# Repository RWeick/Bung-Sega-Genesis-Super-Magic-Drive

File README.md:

# Bung-Sega-Genesis-Super-Magic-Drive
The bioses and Kicad files for the Bung Super Magic Drive for the Sega Genesis

PCB Thicknesses are documented in the Kicad files.

The motherboard contains two modifications from the original: a bodged resistor pack now has its own footprint and there is a solder jumper to switch between original 16M RAM mode and 32M RAM mode. The 32M RAM mode was a modification that would be done when you sent your system back to Bung for the upgrade. Unfortunately it appears that the upgrade also required the CPLD to be upgraded as well, and a modified CPLD has not yet surfaced to be studied. The upgrade solder jumper and 32M RAM board are therefore provided for a future point where the CPLD is found, studied, and reverse engineered. You may use a 32M RAM card with this system, but it will only register 16M of RAM.

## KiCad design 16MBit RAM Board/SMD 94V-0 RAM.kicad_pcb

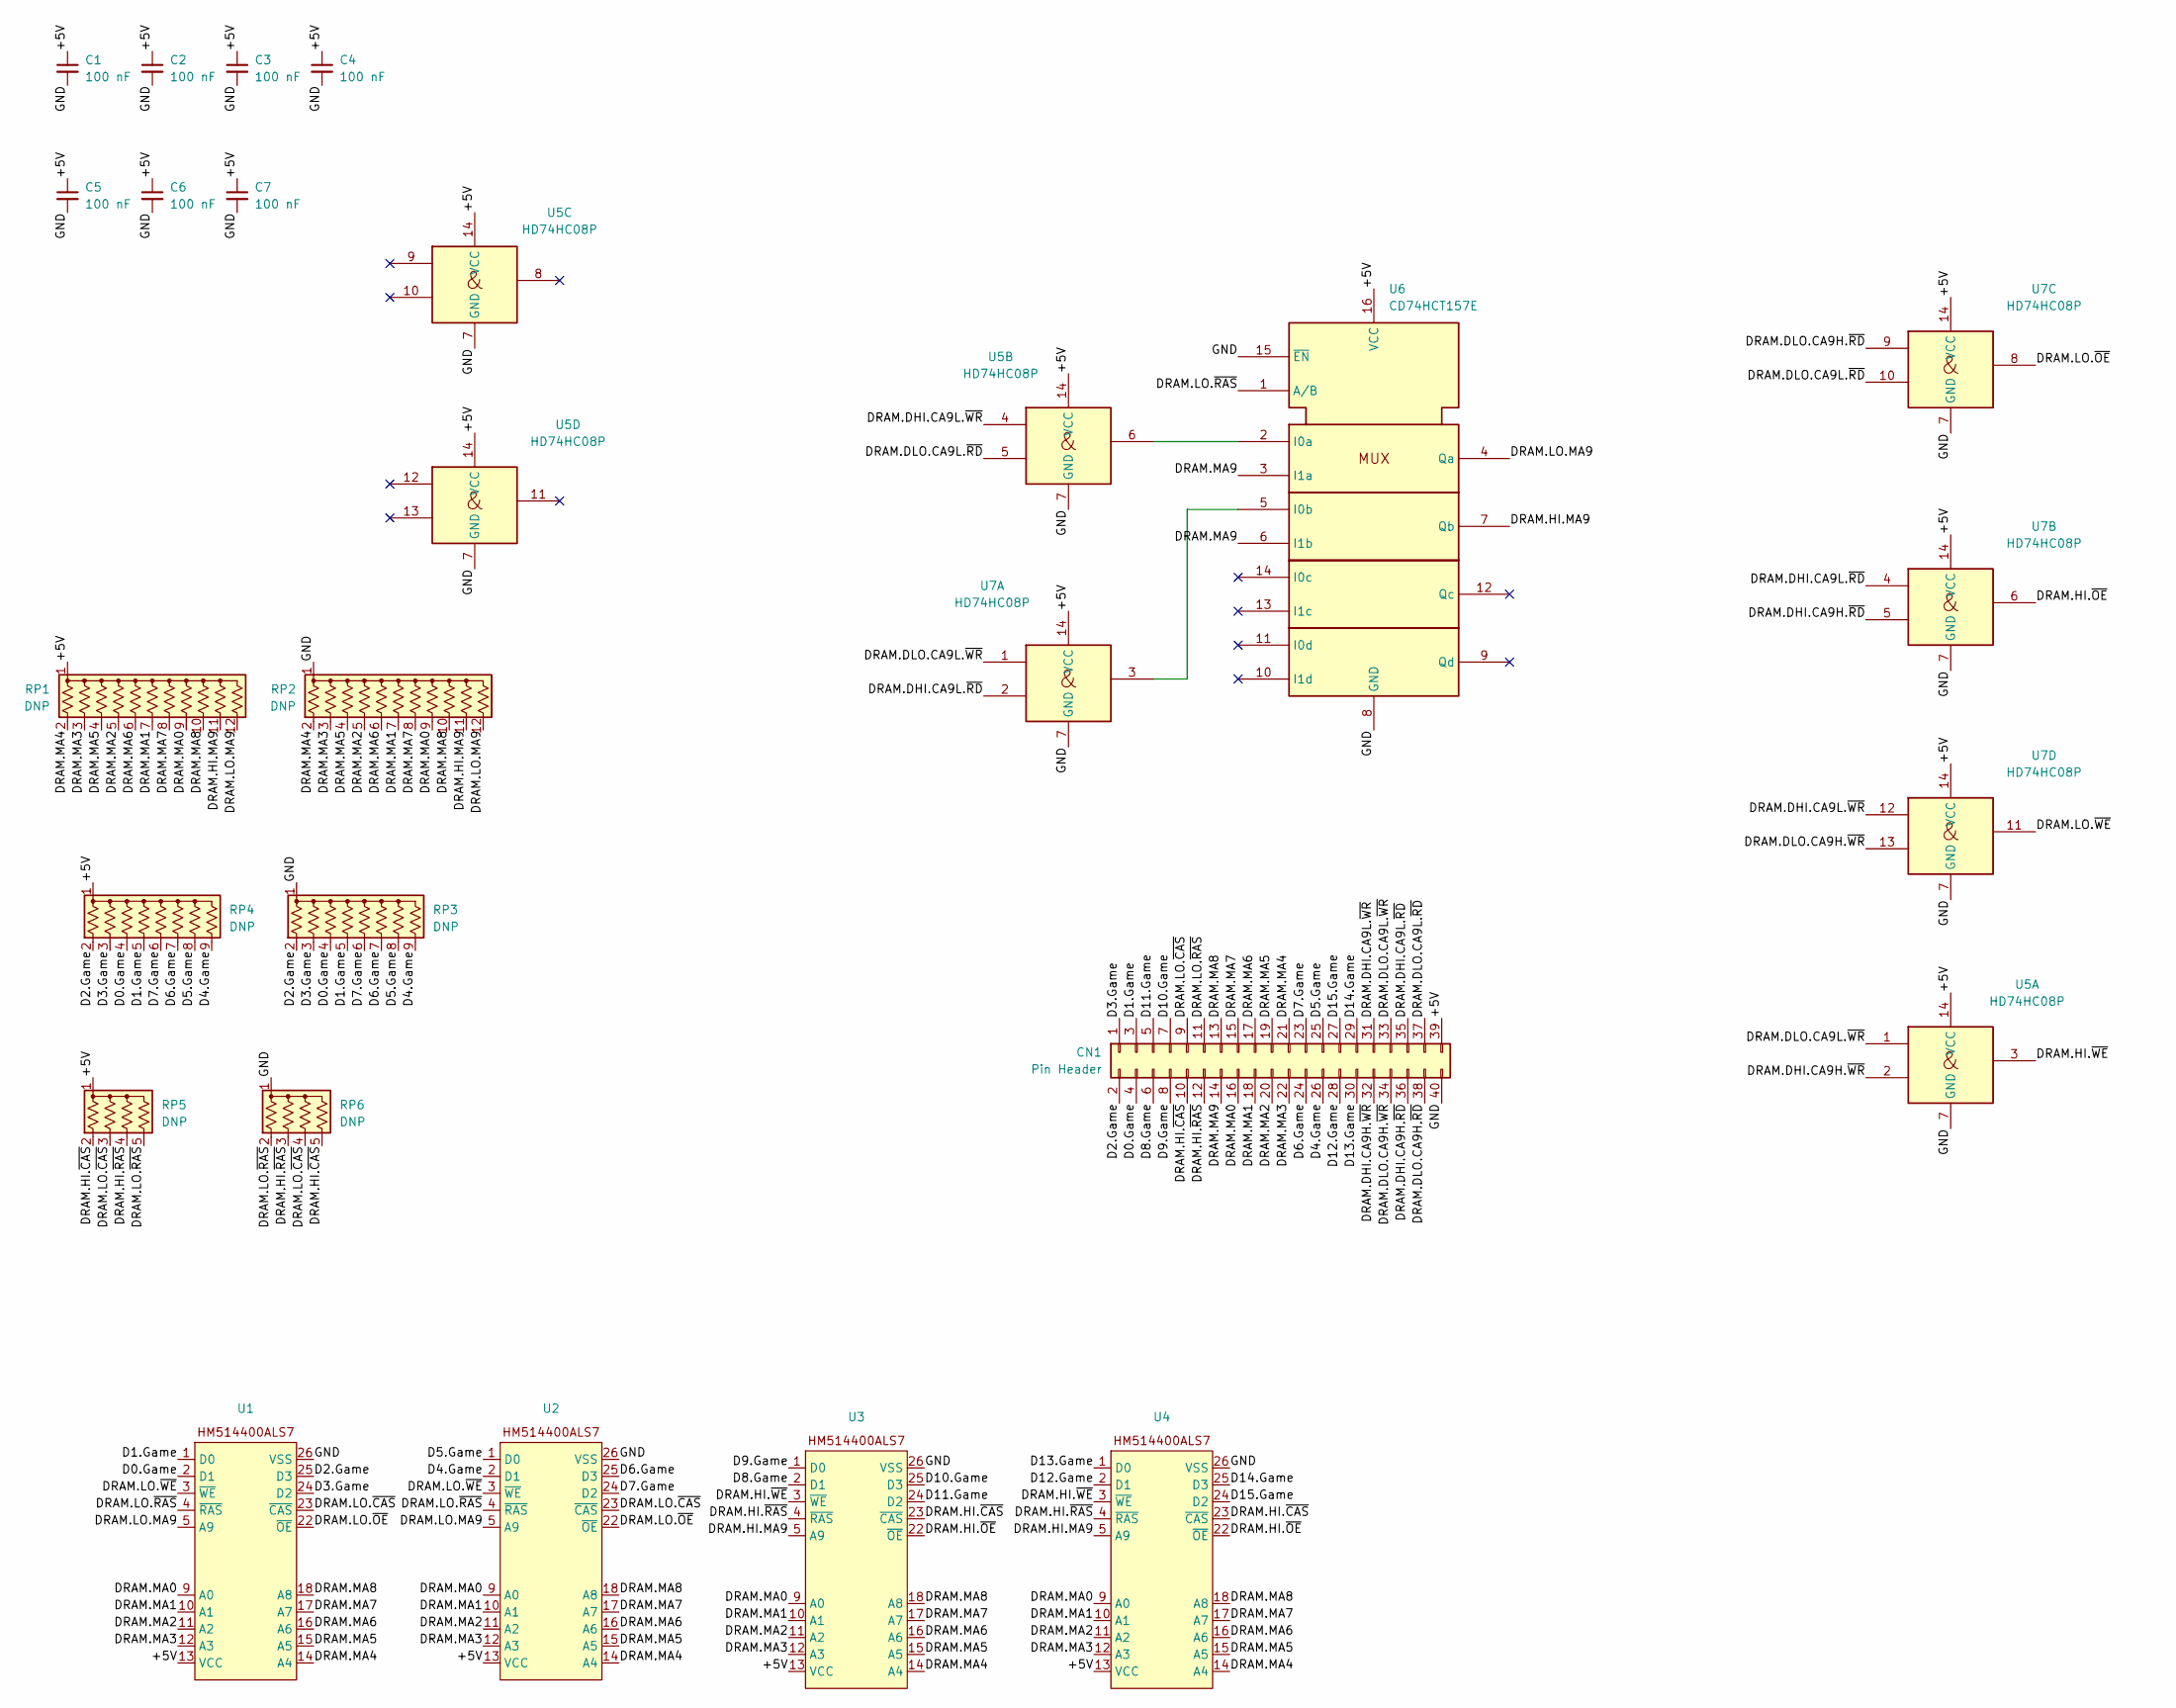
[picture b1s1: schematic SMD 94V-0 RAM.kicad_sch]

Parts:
C1, C2, C3, C4, C5, C6, C7: 100 nF
CN1: Pin Header
RP1, RP2: DNP; R_Array_SIP12
RP3, RP4: DNP; R_Array_SIP9
RP5, RP6: DNP; R_Array_SIP5
U1, U2, U3, U4: (no value)
U5, U7: HD74HC08P
U6: CD74HCT157E

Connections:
/+5V: C1.1, C2.1, C3.1, C4.1, C5.1, C6.1, C7.1, CN1.39, RP1.1 (common), RP4.1 (common), RP5.1 (common), U1.13 (VCC), U2.13 (VCC), U3.13 (VCC), U4.13 (VCC), U5.14 (VCC), U6.16 (VCC), U7.14 (VCC)
/A0: CN1.16, RP1.9 (R8), RP2.9 (R8), U1.9 (A0), U2.9 (A0), U3.9 (A0), U4.9 (A0)
/A1: CN1.18, RP1.7 (R6), RP2.7 (R6), U1.10 (A1), U2.10 (A1), U3.10 (A1), U4.10 (A1)
/A2: CN1.20, RP1.5 (R4), RP2.5 (R4), U1.11 (A2), U2.11 (A2), U3.11 (A2), U4.11 (A2)
/A3: CN1.22, RP1.3 (R2), RP2.3 (R2), U1.12 (A3), U2.12 (A3), U3.12 (A3), U4.12 (A3)
/A4: CN1.21, RP1.2 (R1), RP2.2 (R1), U1.14 (A4), U2.14 (A4), U3.14 (A4), U4.14 (A4)
/A5: CN1.19, RP1.4 (R3), RP2.4 (R3), U1.15 (A5), U2.15 (A5), U3.15 (A5), U4.15 (A5)
/A6: CN1.17, RP1.6 (R5), RP2.6 (R5), U1.16 (A6), U2.16 (A6), U3.16 (A6), U4.16 (A6)
/A7: CN1.15, RP1.8 (R7), RP2.8 (R7), U1.17 (A7), U2.17 (A7), U3.17 (A7), U4.17 (A7)
/A8: CN1.13, RP1.10 (R9), RP2.10 (R9), U1.18 (A8), U2.18 (A8), U3.18 (A8), U4.18 (A8)
/A9: CN1.14, U6.3 (I1a), U6.6 (I1b)
/GND: C1.2, C2.2, C3.2, C4.2, C5.2, C6.2, C7.2, CN1.40, RP2.1 (common), RP3.1 (common), RP6.1 (common), U1.26 (VSS), U2.26 (VSS), U3.26 (VSS), U4.26 (VSS), U5.7 (GND), U6.8 (GND), U6.15 (~EN), U7.7 (GND)
/RAM1-2.~OE: CN1.38, U7.9
/RAM3-4.~OE: CN1.36, U7.5
/RAM.Bank.1.~OE: CN1.35, U7.2, U7.4
/RAM.Bank.1.~WE: CN1.34, U7.13
/RAM.Bank.2.~OE: CN1.37, U5.5, U7.10
/RAM.Bank.2.~WE: CN1.32, U5.2
/U1-2.A9.~WE.EN: CN1.31, U5.4, U7.12
/U1-U2.A9: RP1.12 (R11), RP2.12 (R11), U1.5 (A9), U2.5 (A9), U6.4 (Qa)
/U1-U2.~CAS: CN1.9, RP5.3 (R2), RP6.4 (R3), U1.23 (~CAS), U2.23 (~CAS)
/U1-U2.~OE: U1.22 (~OE), U2.22 (~OE), U7.8
/U1-U2.~RAS: CN1.11, RP5.5 (R4), RP6.2 (R1), U1.4 (~RAS), U2.4 (~RAS), U6.1 (A/B)
/U1-U2.~WE: U1.3 (~WE), U2.3 (~WE), U7.11
/U1.D0: CN1.3, RP3.5 (R4), RP4.5 (R4), U1.1 (D0)
/U1.D1: CN1.4, RP3.4 (R3), RP4.4 (R3), U1.2 (D1)
/U1.D2: CN1.1, RP3.3 (R2), RP4.3 (R2), U1.24 (D2)
/U1.D3: CN1.2, RP3.2 (R1), RP4.2 (R1), U1.25 (D3)
/U2.D0: CN1.25, RP3.8 (R7), RP4.8 (R7), U2.1 (D0)
/U2.D1: CN1.26, RP3.9 (R8), RP4.9 (R8), U2.2 (D1)
/U2.D2: CN1.23, RP3.6 (R5), RP4.6 (R5), U2.24 (D2)
/U2.D3: CN1.24, RP3.7 (R6), RP4.7 (R6), U2.25 (D3)
/U3-4.A9.~WE.EN: CN1.33, U5.1, U7.1
/U3-U4.A9: RP1.11 (R10), RP2.11 (R10), U3.5 (A9), U4.5 (A9), U6.7 (Qb)
/U3-U4.~CAS: CN1.10, RP5.2 (R1), RP6.5 (R4), U3.23 (~CAS), U4.23 (~CAS)
/U3-U4.~OE: U3.22 (~OE), U4.22 (~OE), U7.6
/U3-U4.~RAS: CN1.12, RP5.4 (R3), RP6.3 (R2), U3.4 (~RAS), U4.4 (~RAS)
/U3-U4.~WE: U3.3 (~WE), U4.3 (~WE), U5.3
/U3.D0: CN1.8, U3.1 (D0)
/U3.D1: CN1.6, U3.2 (D1)
/U3.D2: CN1.5, U3.24 (D2)
/U3.D3: CN1.7, U3.25 (D3)
/U4.D0: CN1.30, U4.1 (D0)
/U4.D1: CN1.28, U4.2 (D1)
/U4.D2: CN1.27, U4.24 (D2)
/U4.D3: CN1.29, U4.25 (D3)
unnamed: U5.6, U6.2 (I0a)
unnamed: U6.5 (I0b), U7.3

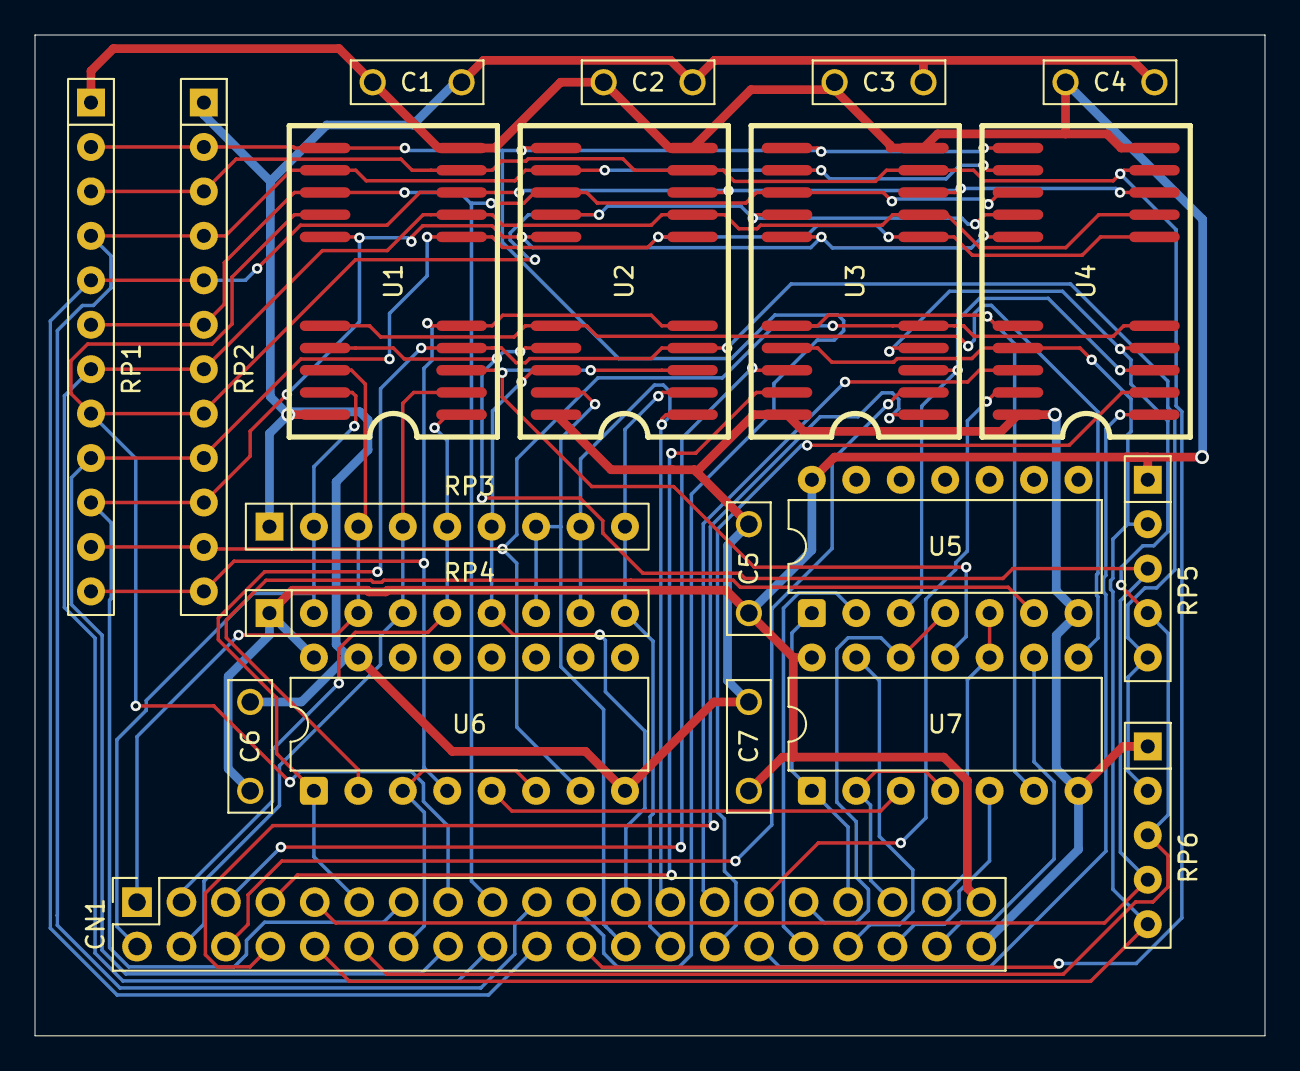
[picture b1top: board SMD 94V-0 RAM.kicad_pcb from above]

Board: 2 copper layers, 70.3 x 57.2 mm, 21 parts (0 on the bottom side), 48 nets.

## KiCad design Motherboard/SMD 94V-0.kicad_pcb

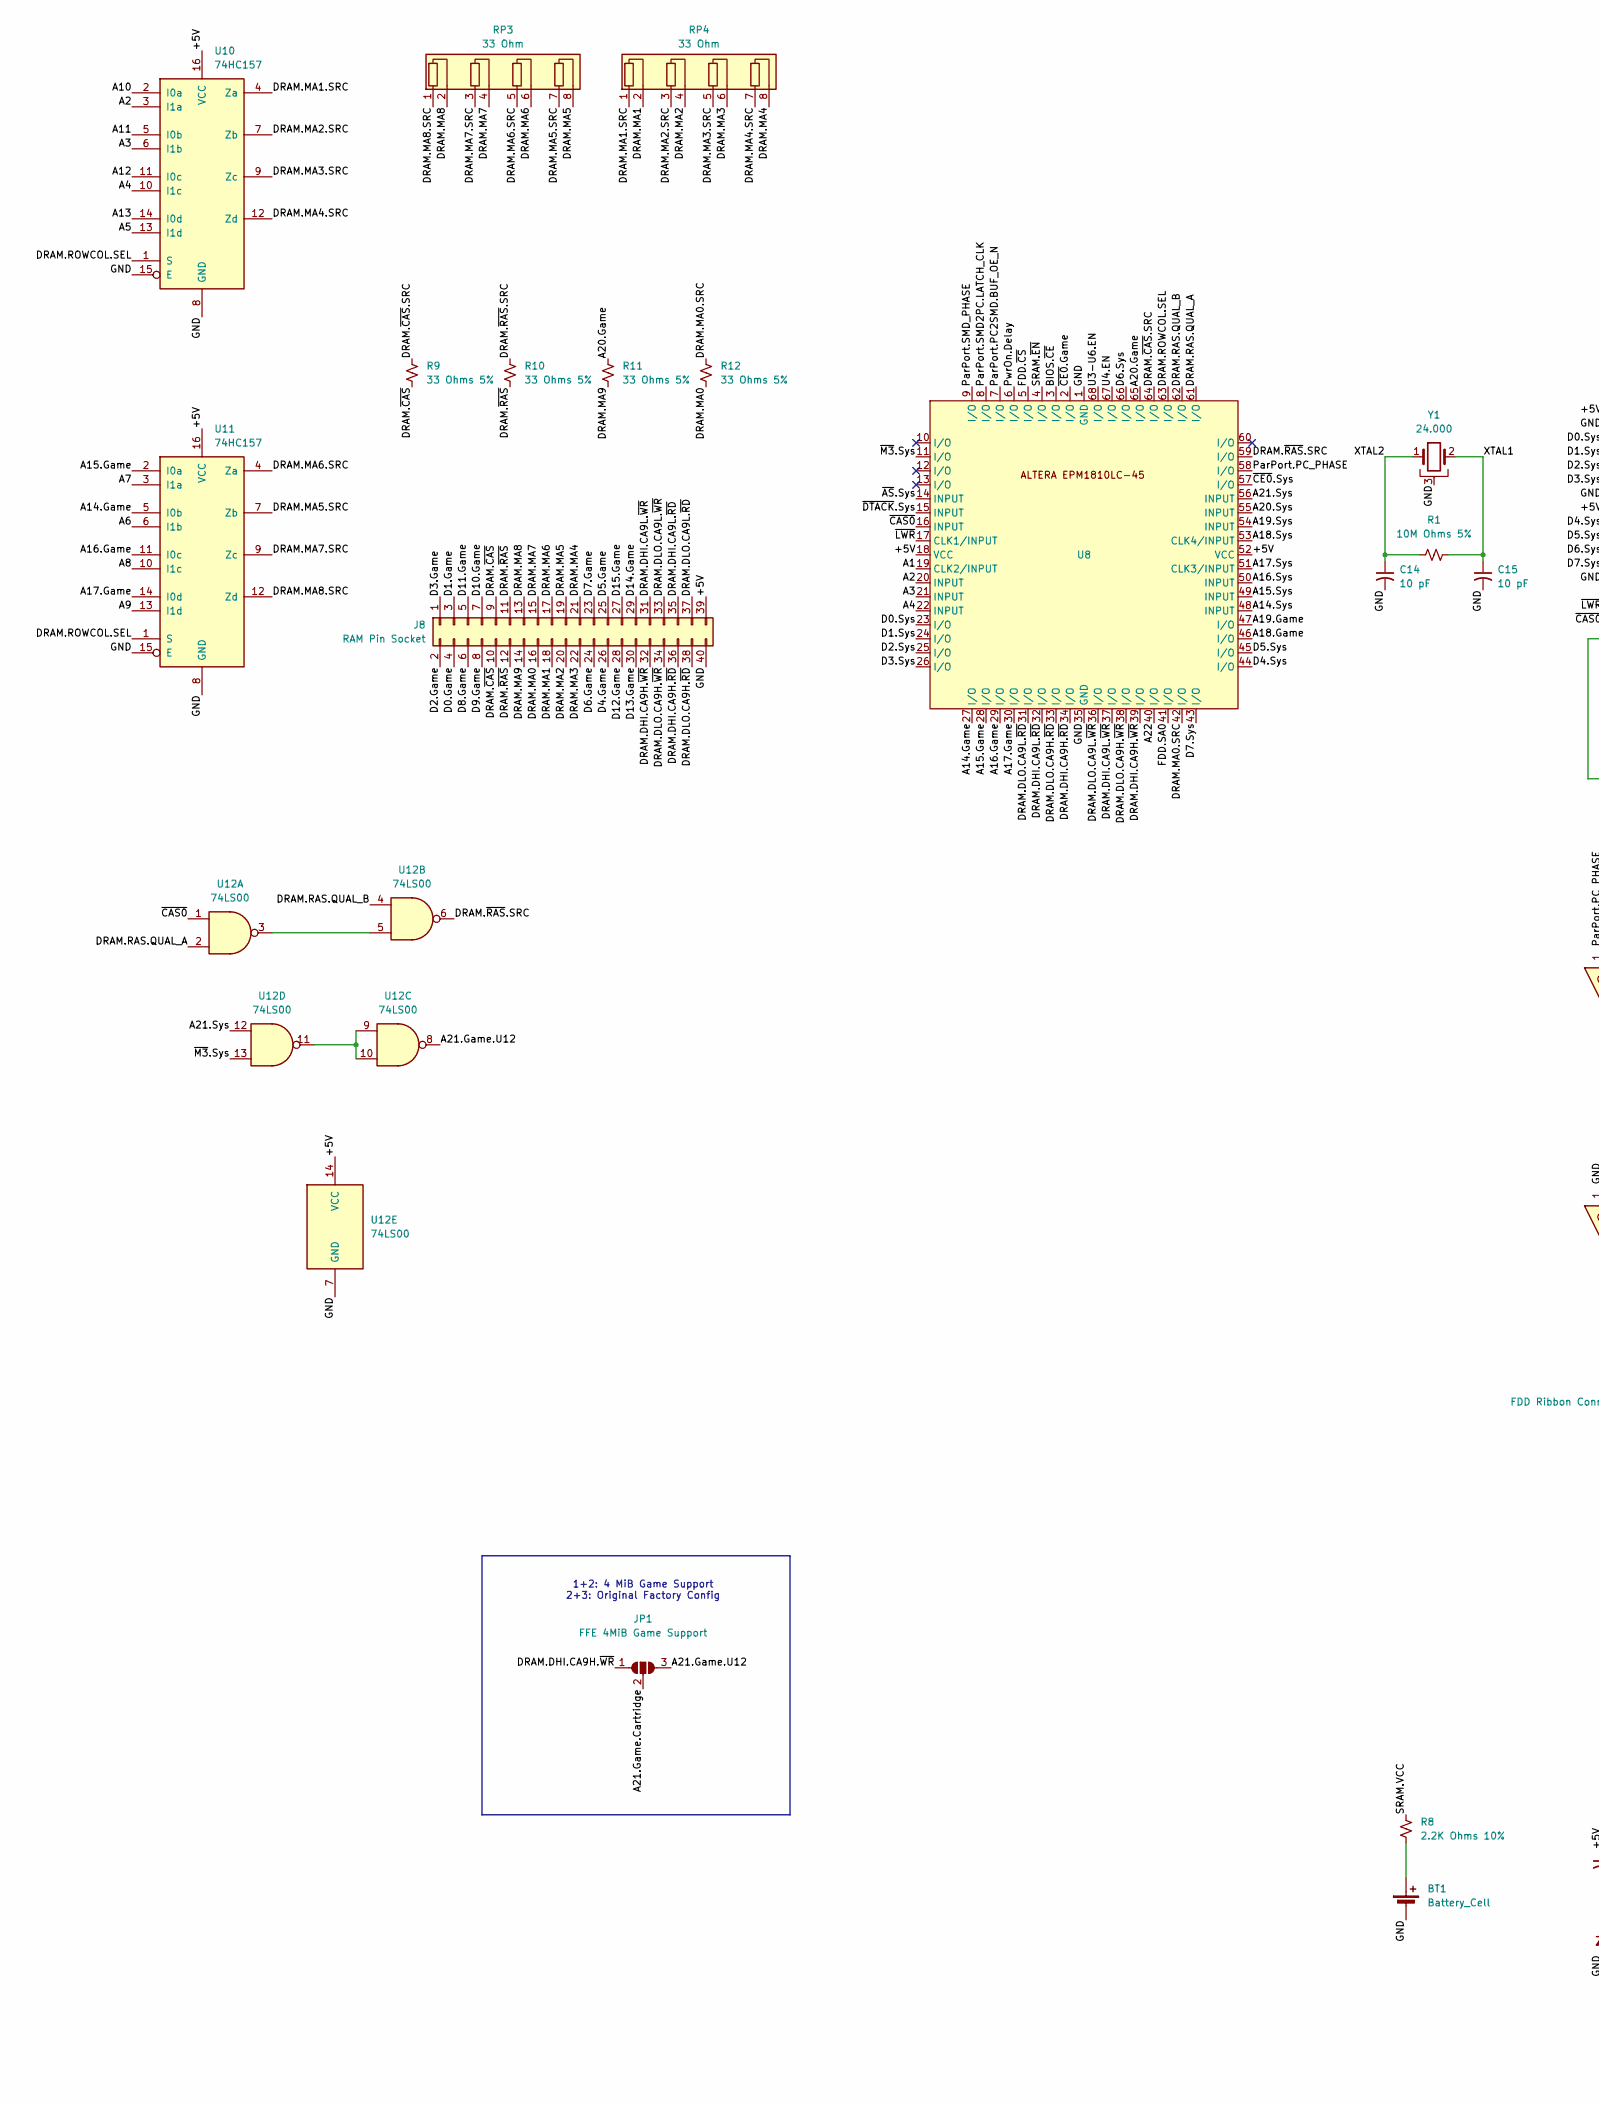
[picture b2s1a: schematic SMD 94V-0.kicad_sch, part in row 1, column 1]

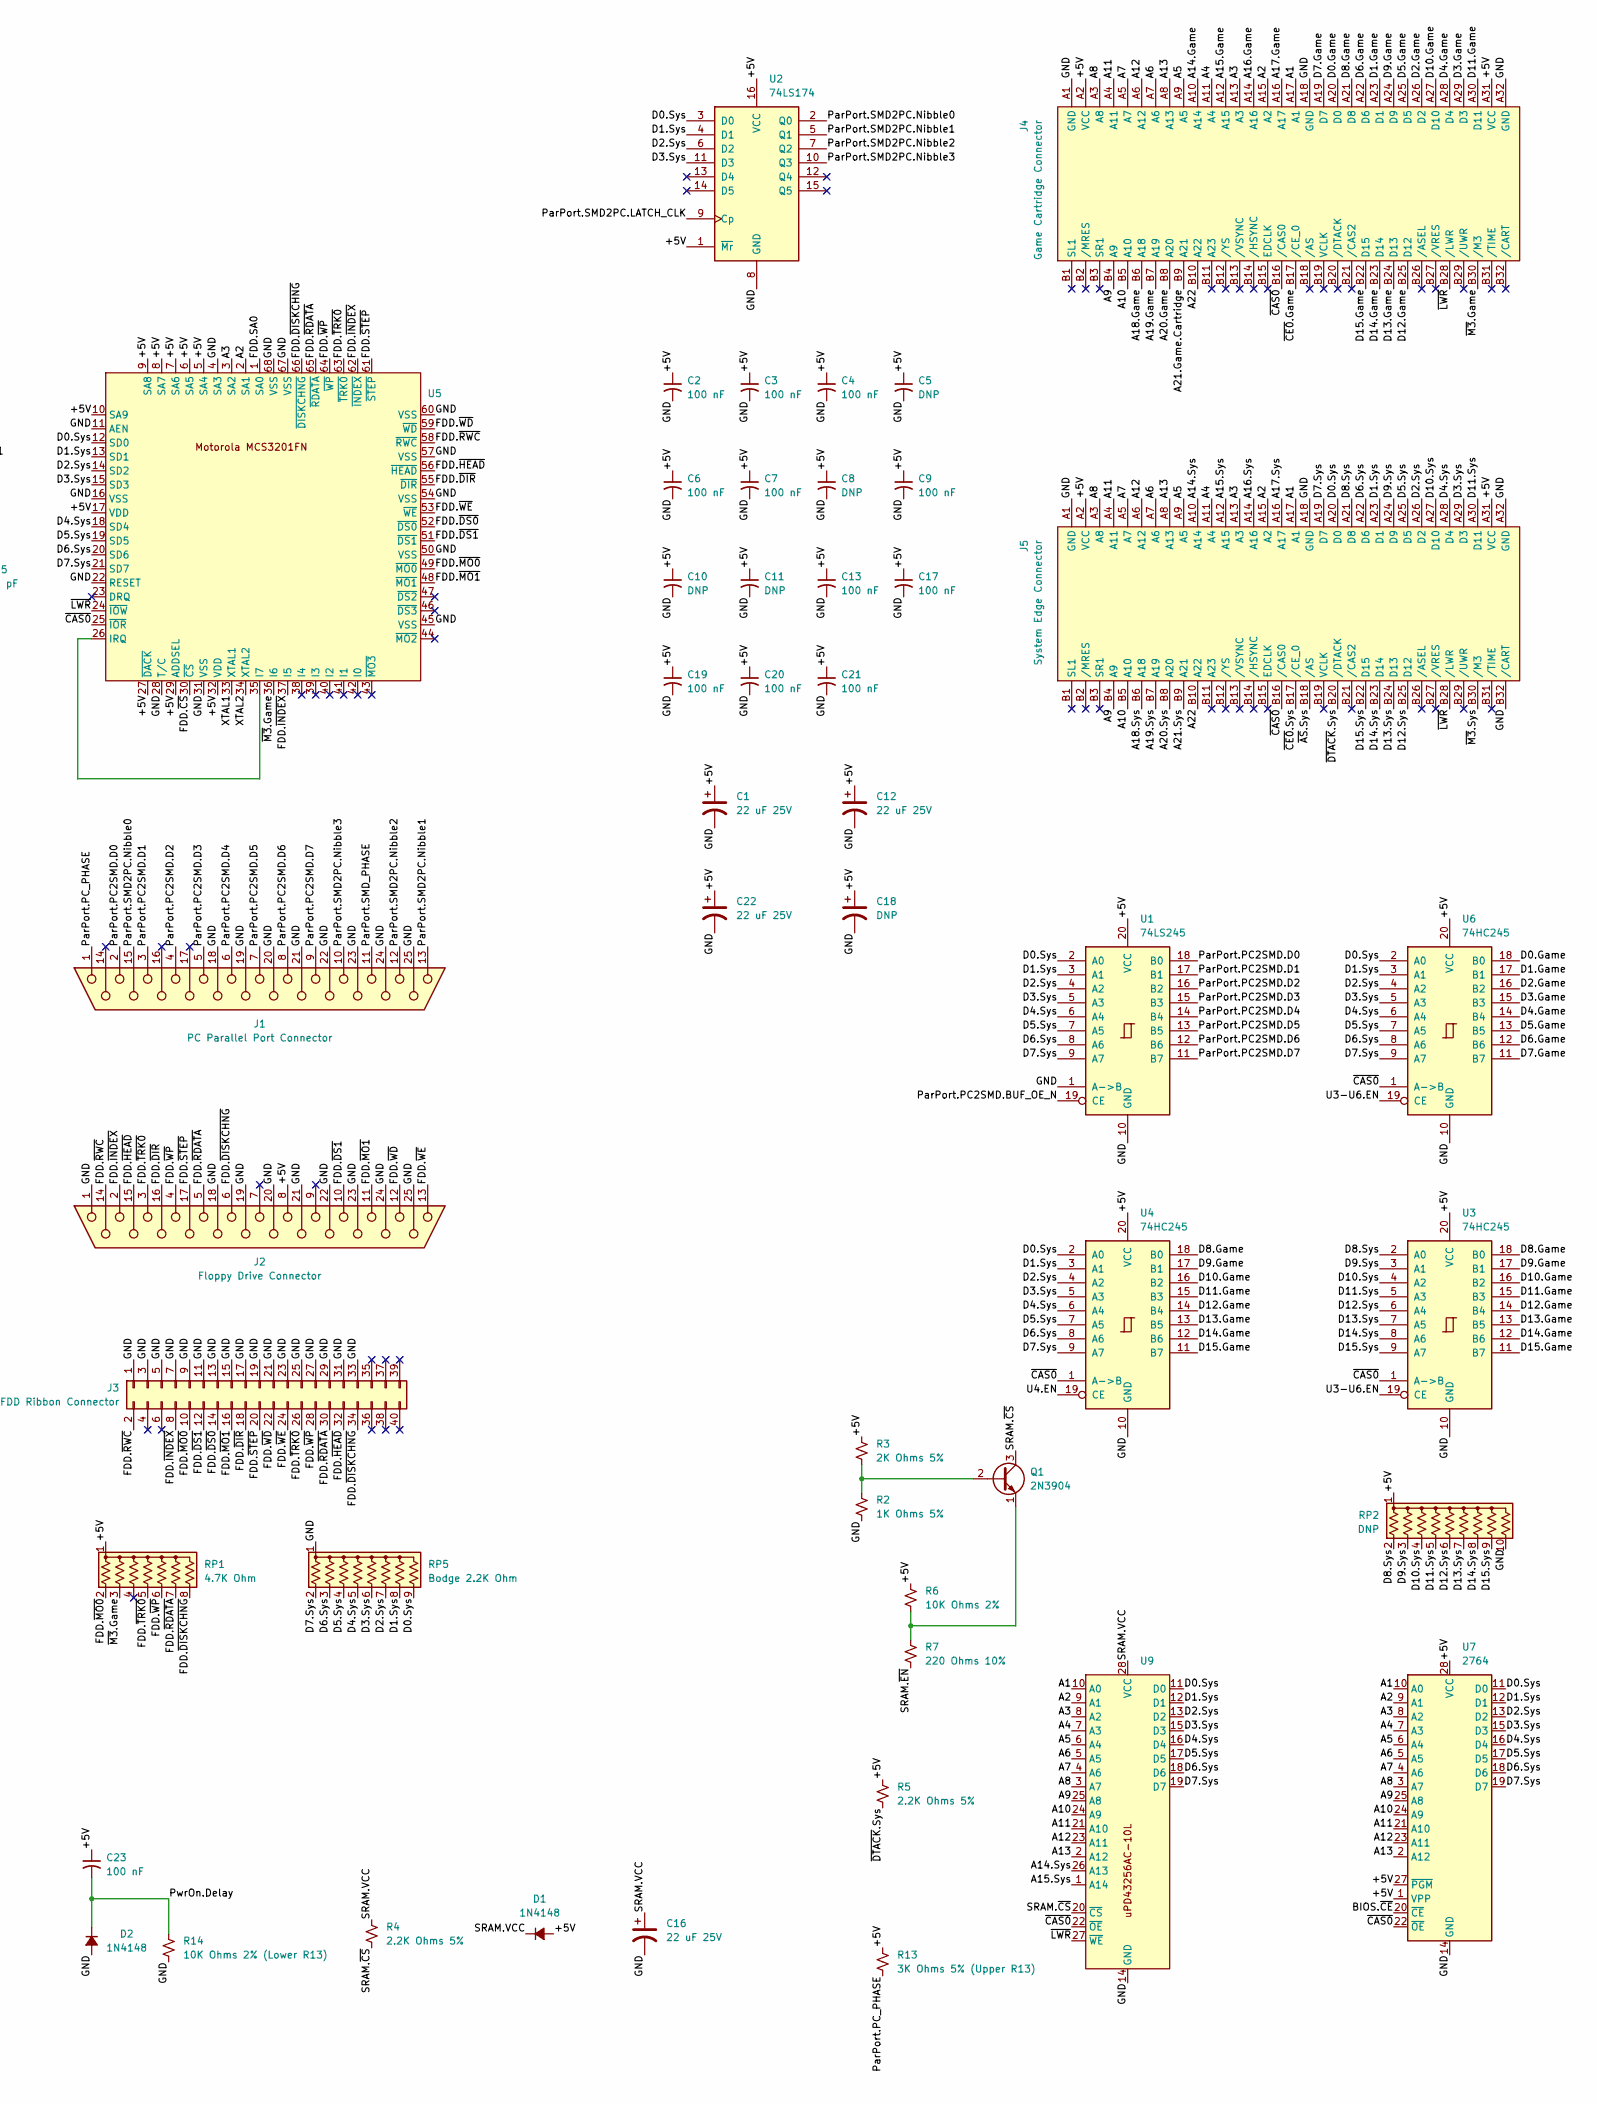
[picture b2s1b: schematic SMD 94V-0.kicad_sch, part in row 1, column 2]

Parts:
BT1: Battery_Cell; Battery
C1, C12, C16, C22: 22 uF 25V; CP_Radial_D5.0mm_P2.50mm
C2, C3, C4, C6, C7, C9, C13, C17, C19, C20, C21, C23: 100 nF; Capacitor
C5, C8, C10, C11: DNP; Capacitor
C14, C15: 10 pF; Capacitor
C18: DNP; CP_Radial_D5.0mm_P2.50mm
D1, D2: 1N4148; Diode
J1: PC Parallel Port Connector; DSUB-25_Socket_Horizontal_P2.77x2.84mm_EdgePinOffset7.70mm_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
J2: Floppy Drive Connector; DSUB-25_Socket_Horizontal_P2.77x2.84mm_EdgePinOffset7.70mm_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
J3: FDD Ribbon Connector; PinHeader_2x20_P2.54mm_Vertical
J4: Game Cartridge Connector; Cartridge Slot
J5: System Edge Connector; PinHeader_2x32_P2.54mm_Vertical
J8: RAM Pin Socket; PinHeader_2x20_P2.54mm_Vertical
JP1: FFE 4MiB Game Support; SolderJumper-3_P1.3mm_Open_RoundedPad1.0x1.5mm_NumberLabels
Q1: 2N3904; Transistor
R1: 10M Ohms 5%; Resistor
R2: 1K Ohms 5%; Resistor
R3: 2K Ohms 5%; Resistor
R4, R5: 2.2K Ohms 5%; Resistor
R6: 10K Ohms 2%; Resistor
R7: 220 Ohms 10%; Resistor
R8: 2.2K Ohms 10%; Resistor
R9, R10, R11, R12: 33 Ohms 5%; Resistor
R13: 3K Ohms 5% (Upper R13); Resistor
R14: 10K Ohms 2% (Lower R13); Resistor
RP1: 4.7K Ohm; R_Array_SIP8
RP2: DNP; R_Array_SIP10
RP3, RP4: 33 Ohm; R_Array_SIP8
RP5: Bodge 2.2K Ohm; R_Array_SIP9
U1: 74LS245; DIP-20_W7.62mm
U2: 74LS174; DIP-16_W7.62mm
U3, U4, U6: 74HC245; DIP-20_W7.62mm
U5, U8: PLCC-68_THT-Socket
U7: 2764; DIP-28_W15.24mm
U9: DIP-28_W15.24mm
U10, U11: 74HC157; DIP-16_W7.62mm
U12: 74LS00; DIP-14_W7.62mm
Y1: 24.000; Crystal_HC18-U_Horizontal_1EP_style2

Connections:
/+5V: C1.1, C2.1, C3.1, C4.1, C5.1, C6.1, C7.1, C8.1, C9.1, C10.1, C11.1, C12.1, C13.1, C17.1, C18.1, C19.1, C20.1, C21.1, C22.1, C23.1, D1.2 (A), J2.8, J4.A2 (VCC), J4.A31 (VCC), J5.A2 (VCC), J5.A31 (VCC), J8.39, R3.1, R5.1, R6.1, R13.1, RP1.1 (common), RP2.1 (common), U1.20 (VCC), U2.1 (~Mr), U2.16 (VCC), U3.20 (VCC), U4.20 (VCC), U5.5 (SA4), U5.6 (SA5), U5.7 (SA6), U5.8 (SA7), U5.9 (SA8), U5.10 (SA9), U5.17 (VDD), U5.27 (~DACK), U5.29 (ADDSEL), U5.32 (VDD), U6.20 (VCC), U7.1 (VPP), U7.27 (~PGM), U7.28 (VCC), U8.18 (VCC), U8.52 (VCC), U10.16 (VCC), U11.16 (VCC), U12.14 (VCC)
/A1: J4.A17 (A1), J5.A17 (A1), U7.10 (A0), U8.19 (CLK2/INPUT), U9.10 (A0)
/A2: J4.A15 (A2), J5.A15 (A2), U5.2 (SA1), U7.9 (A1), U8.20 (INPUT), U9.9 (A1), U10.3 (I1a)
/A3: J4.A13 (A3), J5.A13 (A3), U5.3 (SA2), U7.8 (A2), U8.21 (INPUT), U9.8 (A2), U10.6 (I1b)
/A4: J4.A11 (A4), J5.A11 (A4), U7.7 (A3), U8.22 (INPUT), U9.7 (A3), U10.10 (I1c)
/A5: J4.A9 (A5), J5.A9 (A5), U7.6 (A4), U9.6 (A4), U10.13 (I1d)
/A6: J4.A7 (A6), J5.A7 (A6), U7.5 (A5), U9.5 (A5), U11.6 (I1b)
/A7: J4.A5 (A7), J5.A5 (A7), U7.4 (A6), U9.4 (A6), U11.3 (I1a)
/A8: J4.A3 (A8), J5.A3 (A8), U7.3 (A7), U9.3 (A7), U11.10 (I1c)
/A9: J4.B4 (A9), J5.B4 (A9), U7.25 (A8), U9.25 (A8), U11.13 (I1d)
/A10: J4.B5 (A10), J5.B5 (A10), U7.24 (A9), U9.24 (A9), U10.2 (I0a)
/A11: J4.A4 (A11), J5.A4 (A11), U7.21 (A10), U9.21 (A10), U10.5 (I0b)
/A12: J4.A6 (A12), J5.A6 (A12), U7.23 (A11), U9.23 (A11), U10.11 (I0c)
/A13: J4.A8 (A13), J5.A8 (A13), U7.2 (A12), U9.2 (A12), U10.14 (I0d)
/A14.Game: J4.A10 (A14), U8.27 (I/O), U11.5 (I0b)
/A14.Sys: J5.A10 (A14), U8.48 (INPUT), U9.26 (A13)
/A15.Game: J4.A12 (A15), U8.28 (I/O), U11.2 (I0a)
/A15.Sys: J5.A12 (A15), U8.49 (INPUT), U9.1 (A14)
/A16.Game: J4.A14 (A16), U8.29 (I/O), U11.11 (I0c)
/A16.Sys: J5.A14 (A16), U8.50 (INPUT)
/A17.Game: J4.A16 (A17), U8.30 (I/O), U11.14 (I0d)
/A17.Sys: J5.A16 (A17), U8.51 (CLK3/INPUT)
/A18.Game: J4.B6 (A18), U8.46 (I/O)
/A18.Sys: J5.B6 (A18), U8.53 (CLK4/INPUT)
/A19.Game: J4.B7 (A19), U8.47 (I/O)
/A19.Sys: J5.B7 (A19), U8.54 (INPUT)
/A20.Game: J4.B8 (A20), R11.1, U8.65 (I/O)
/A20.Sys: J5.B8 (A20), U8.55 (INPUT)
/A21.Game.Cartridge: J4.B9 (A21), JP1.2 (C)
/A21.Game.U12: JP1.3 (B), U12.8
/A21.Sys: J5.B9 (A21), U8.56 (INPUT), U12.12
/A22: J4.B10 (A22), J5.B10 (A22), U8.40 (I/O)
/BIOS.~CE: U7.20 (~CE), U8.3 (I/O)
/D0.Game: J4.A20 (D0), J8.4, U6.18 (B0)
/D0.Sys: J5.A20 (D0), RP5.9 (R8), U1.2 (A0), U2.3 (D0), U4.2 (A0), U5.12 (SD0), U6.2 (A0), U7.11 (D0), U8.23 (I/O), U9.11 (D0)
/D1.Game: J4.A23 (D1), J8.3, U6.17 (B1)
/D1.Sys: J5.A23 (D1), RP5.8 (R7), U1.3 (A1), U2.4 (D1), U4.3 (A1), U5.13 (SD1), U6.3 (A1), U7.12 (D1), U8.24 (I/O), U9.12 (D1)
/D2.Game: J4.A26 (D2), J8.2, U6.16 (B2)
/D2.Sys: J5.A26 (D2), RP5.7 (R6), U1.4 (A2), U2.6 (D2), U4.4 (A2), U5.14 (SD2), U6.4 (A2), U7.13 (D2), U8.25 (I/O), U9.13 (D2)
/D3.Game: J4.A29 (D3), J8.1, U6.15 (B3)
/D3.Sys: J5.A29 (D3), RP5.6 (R5), U1.5 (A3), U2.11 (D3), U4.5 (A3), U5.15 (SD3), U6.5 (A3), U7.15 (D3), U8.26 (I/O), U9.15 (D3)
/D4.Game: J4.A28 (D4), J8.26, U6.14 (B4)
/D4.Sys: J5.A28 (D4), RP5.5 (R4), U1.6 (A4), U4.6 (A4), U5.18 (SD4), U6.6 (A4), U7.16 (D4), U8.44 (I/O), U9.16 (D4)
/D5.Game: J4.A25 (D5), J8.25, U6.13 (B5)
/D5.Sys: J5.A25 (D5), RP5.4 (R3), U1.7 (A5), U4.7 (A5), U5.19 (SD5), U6.7 (A5), U7.17 (D5), U8.45 (I/O), U9.17 (D5)
/D6.Game: J4.A22 (D6), J8.24, U6.12 (B6)
/D6.Sys: J5.A22 (D6), RP5.3 (R2), U1.8 (A6), U4.8 (A6), U5.20 (SD6), U6.8 (A6), U7.18 (D6), U8.66 (I/O), U9.18 (D6)
/D7.Game: J4.A19 (D7), J8.23, U6.11 (B7)
/D7.Sys: J5.A19 (D7), RP5.2 (R1), U1.9 (A7), U4.9 (A7), U5.21 (SD7), U6.9 (A7), U7.19 (D7), U8.43 (I/O), U9.19 (D7)
/D8.Game: J4.A21 (D8), J8.6, U3.18 (B0), U4.18 (B0)
/D8.Sys: J5.A21 (D8), RP2.2 (R1), U3.2 (A0)
/D9.Game: J4.A24 (D9), J8.8, U3.17 (B1), U4.17 (B1)
/D9.Sys: J5.A24 (D9), RP2.3 (R2), U3.3 (A1)
/D10.Game: J4.A27 (D10), J8.7, U3.16 (B2), U4.16 (B2)
/D10.Sys: J5.A27 (D10), RP2.4 (R3), U3.4 (A2)
/D11.Game: J4.A30 (D11), J8.5, U3.15 (B3), U4.15 (B3)
/D11.Sys: J5.A30 (D11), RP2.5 (R4), U3.5 (A3)
/D12.Game: J4.B25 (D12), J8.28, U3.14 (B4), U4.14 (B4)
/D12.Sys: J5.B25 (D12), RP2.6 (R5), U3.6 (A4)
/D13.Game: J4.B24 (D13), J8.30, U3.13 (B5), U4.13 (B5)
/D13.Sys: J5.B24 (D13), RP2.7 (R6), U3.7 (A5)
/D14.Game: J4.B23 (D14), J8.29, U3.12 (B6), U4.12 (B6)
/D14.Sys: J5.B23 (D14), RP2.8 (R7), U3.8 (A6)
/D15.Game: J4.B22 (D15), J8.27, U3.11 (B7), U4.11 (B7)
/D15.Sys: J5.B22 (D15), RP2.9 (R8), U3.9 (A7)
/DRAM.DHI.CA9H.~RD: J8.36, U8.34 (I/O)
/DRAM.DHI.CA9H.~WR: J8.32, JP1.1 (A), U8.39 (I/O)
/DRAM.DHI.CA9L.~RD: J8.35, U8.32 (I/O)
/DRAM.DHI.CA9L.~WR: J8.31, U8.37 (I/O)
/DRAM.DLO.CA9H.~RD: J8.38, U8.33 (I/O)
/DRAM.DLO.CA9H.~WR: J8.34, U8.38 (I/O)
/DRAM.DLO.CA9L.~RD: J8.37, U8.31 (I/O)
/DRAM.DLO.CA9L.~WR: J8.33, U8.36 (I/O)
/DRAM.MA0: J8.16, R12.2
/DRAM.MA0.SRC: R12.1, U8.42 (I/O)
/DRAM.MA1: J8.18, RP4.2 (R1.2)
/DRAM.MA1.SRC: RP4.1 (R1.1), U10.4 (Za)
/DRAM.MA2: J8.20, RP4.4 (R2.2)
/DRAM.MA2.SRC: RP4.3 (R2.1), U10.7 (Zb)
/DRAM.MA3: J8.22, RP4.6 (R3.2)
/DRAM.MA3.SRC: RP4.5 (R3.1), U10.9 (Zc)
/DRAM.MA4: J8.21, RP4.8 (R4.2)
/DRAM.MA4.SRC: RP4.7 (R4.1), U10.12 (Zd)
/DRAM.MA5: J8.19, RP3.8 (R4.2)
/DRAM.MA5.SRC: RP3.7 (R4.1), U11.7 (Zb)
/DRAM.MA6: J8.17, RP3.6 (R3.2)
/DRAM.MA6.SRC: RP3.5 (R3.1), U11.4 (Za)
/DRAM.MA7: J8.15, RP3.4 (R2.2)
/DRAM.MA7.SRC: RP3.3 (R2.1), U11.9 (Zc)
/DRAM.MA8: J8.13, RP3.2 (R1.2)
/DRAM.MA8.SRC: RP3.1 (R1.1), U11.12 (Zd)
/DRAM.MA9: J8.14, R11.2
/DRAM.RAS.QUAL_A: U8.61 (I/O), U12.2
/DRAM.RAS.QUAL_B: U8.62 (I/O), U12.4
/DRAM.ROWCOL.SEL: U8.63 (I/O), U10.1 (S), U11.1 (S)
/DRAM.~CAS: J8.9, J8.10, R9.2
/DRAM.~CAS.SRC: R9.1, U8.64 (I/O)
/DRAM.~RAS: J8.11, J8.12, R10.2
/DRAM.~RAS.SRC: R10.1, U8.59 (I/O), U12.6
/FDD.SA0: U5.1 (SA0), U8.41 (I/O)
/FDD.~CS: U5.30 (~CS), U8.5 (I/O)
/FDD.~DIR: J2.16, J3.18, U5.55 (~DIR)
/FDD.~DISKCHNG: J2.6, J3.34, RP1.8 (R7), U5.66 (~DISKCHNG)
/FDD.~DS0: J3.14, U5.52 (~DS0)
/FDD.~DS1: J2.10, J3.12, U5.51 (~DS1)
/FDD.~HEAD: J2.15, J3.32, U5.56 (~HEAD)
/FDD.~INDEX: J2.2, J3.8, U5.37 (I5), U5.62 (~INDEX)
/FDD.~MO0: J3.10, RP1.2 (R1), U5.49 (~MO0)
/FDD.~MO1: J2.11, J3.16, U5.48 (~MO1)
/FDD.~RDATA: J2.5, J3.30, RP1.7 (R6), U5.65 (~RDATA)
/FDD.~RWC: J2.14, J3.2, U5.58 (~RWC)
/FDD.~STEP: J2.17, J3.20, U5.61 (~STEP)
/FDD.~TRK0: J2.3, J3.26, RP1.5 (R4), U5.63 (~TRK0)
/FDD.~WD: J2.12, J3.22, U5.59 (~WD)
/FDD.~WE: J2.13, J3.24, U5.53 (~WE)
/FDD.~WP: J2.4, J3.28, RP1.6 (R5), U5.64 (~WP)
/GND: BT1.2 (-), C1.2, C2.2, C3.2, C4.2, C5.2, C6.2, C7.2, C8.2, C9.2, C10.2, C11.2, C12.2, C13.2, C14.2, C15.2, C16.2, C17.2, C18.2, C19.2, C20.2, C21.2, C22.2, D2.2 (A), J1.18, J1.19, J1.20, J1.21, J1.22, J1.23, J1.24, J1.25, J1.SH, J2.1, J2.18, J2.19, J2.20, J2.21, J2.22, J2.23, J2.24, J2.25, J2.SH, J3.1, J3.3, J3.5, J3.7, J3.9, J3.11, J3.13, J3.15, J3.17, J3.19, J3.21, J3.23, J3.25, J3.27, J3.29, J3.31, J3.33, J4.A1 (GND), J4.A18 (GND), J4.A32 (GND), J5.A1 (GND), J5.A18 (GND), J5.A32 (GND), J5.B32 (/CART), J8.40, R2.2, R14.2, RP2.10 (R9), RP5.1 (common), U1.1 (A->B), U1.10 (GND), U2.8 (GND), U3.10 (GND), U4.10 (GND), U5.4 (SA3), U5.11 (AEN), U5.16 (VSS), U5.22 (RESET), U5.28 (T/C), U5.31 (VSS), U5.45 (VSS), U5.50 (VSS), U5.54 (VSS), U5.57 (VSS), U5.60 (VSS), U5.67 (VSS), U5.68 (VSS), U6.10 (GND), U7.14 (GND), U8.1 (GND), U8.35 (GND), U9.14 (GND), U10.8 (GND), U10.15 (E), U11.8 (GND), U11.15 (E), U12.7 (GND), Y1.3
/ParPort.PC2SMD.BUF_OE_N: U1.19 (CE), U8.7 (I/O)
/ParPort.PC2SMD.D0: J1.2, U1.18 (B0)
/ParPort.PC2SMD.D1: J1.3, U1.17 (B1)
/ParPort.PC2SMD.D2: J1.4, U1.16 (B2)
/ParPort.PC2SMD.D3: J1.5, U1.15 (B3)
/ParPort.PC2SMD.D4: J1.6, U1.14 (B4)
/ParPort.PC2SMD.D5: J1.7, U1.13 (B5)
/ParPort.PC2SMD.D6: J1.8, U1.12 (B6)
/ParPort.PC2SMD.D7: J1.9, U1.11 (B7)
/ParPort.PC_PHASE: J1.1, R13.2, U8.58 (I/O)
/ParPort.SMD2PC.LATCH_CLK: U2.9 (Cp), U8.8 (I/O)
/ParPort.SMD2PC.Nibble0: J1.15, U2.2 (Q0)
/ParPort.SMD2PC.Nibble1: J1.13, U2.5 (Q1)
/ParPort.SMD2PC.Nibble2: J1.12, U2.7 (Q2)
/ParPort.SMD2PC.Nibble3: J1.10, U2.10 (Q3)
/ParPort.SMD_PHASE: J1.11, U8.9 (I/O)
/PwrOn.Delay: C23.2, D2.1 (K), R14.1, U8.6 (I/O)
/SRAM.VCC: C16.1, D1.1 (K), R4.1, R8.1, U9.28 (VCC)
/SRAM.~CS: Q1.3 (C), R4.2, U9.20 (~CS)
/SRAM.~EN: R7.2, U8.4 (I/O)
/U3-U6.EN: U3.19 (CE), U6.19 (CE), U8.68 (I/O)
/U4.EN: U4.19 (CE), U8.67 (I/O)
/XTAL1: C15.1, R1.2, U5.33 (XTAL1), Y1.2
/XTAL2: C14.1, R1.1, U5.34 (XTAL2), Y1.1
/~AS.Sys: J5.B18 (/AS), U8.14 (INPUT)
/~CAS0: J4.B16 (/CAS0), J5.B16 (/CAS0), U3.1 (A->B), U4.1 (A->B), U5.25 (~IOR), U6.1 (A->B), U7.22 (~OE), U8.16 (INPUT), U9.22 (~OE), U12.1
/~CE0.Game: J4.B17 (/CE_0), U8.2 (I/O)
/~CE0.Sys: J5.B17 (/CE_0), U8.57 (I/O)
/~DTACK.Sys: J5.B20 (/DTACK), R5.2, U8.15 (INPUT)
/~LWR: J4.B28 (/LWR), J5.B28 (/LWR), U5.24 (~IOW), U8.17 (CLK1/INPUT), U9.27 (~WE)
/~M3.Game: J4.B30 (/M3), RP1.3 (R2), U5.36 (I6)
/~M3.Sys: J5.B30 (/M3), U8.11 (I/O), U12.13
unnamed: BT1.1 (+), R8.2
unnamed: Q1.2 (B), R2.1, R3.2
unnamed: Q1.1 (E), R6.2, R7.1
unnamed: U5.26 (IRQ), U5.35 (I7)
unnamed: U12.3, U12.5
unnamed: U12.9, U12.10, U12.11

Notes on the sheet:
1+2: 4 MiB Game Support 2+3: Original Factory Config

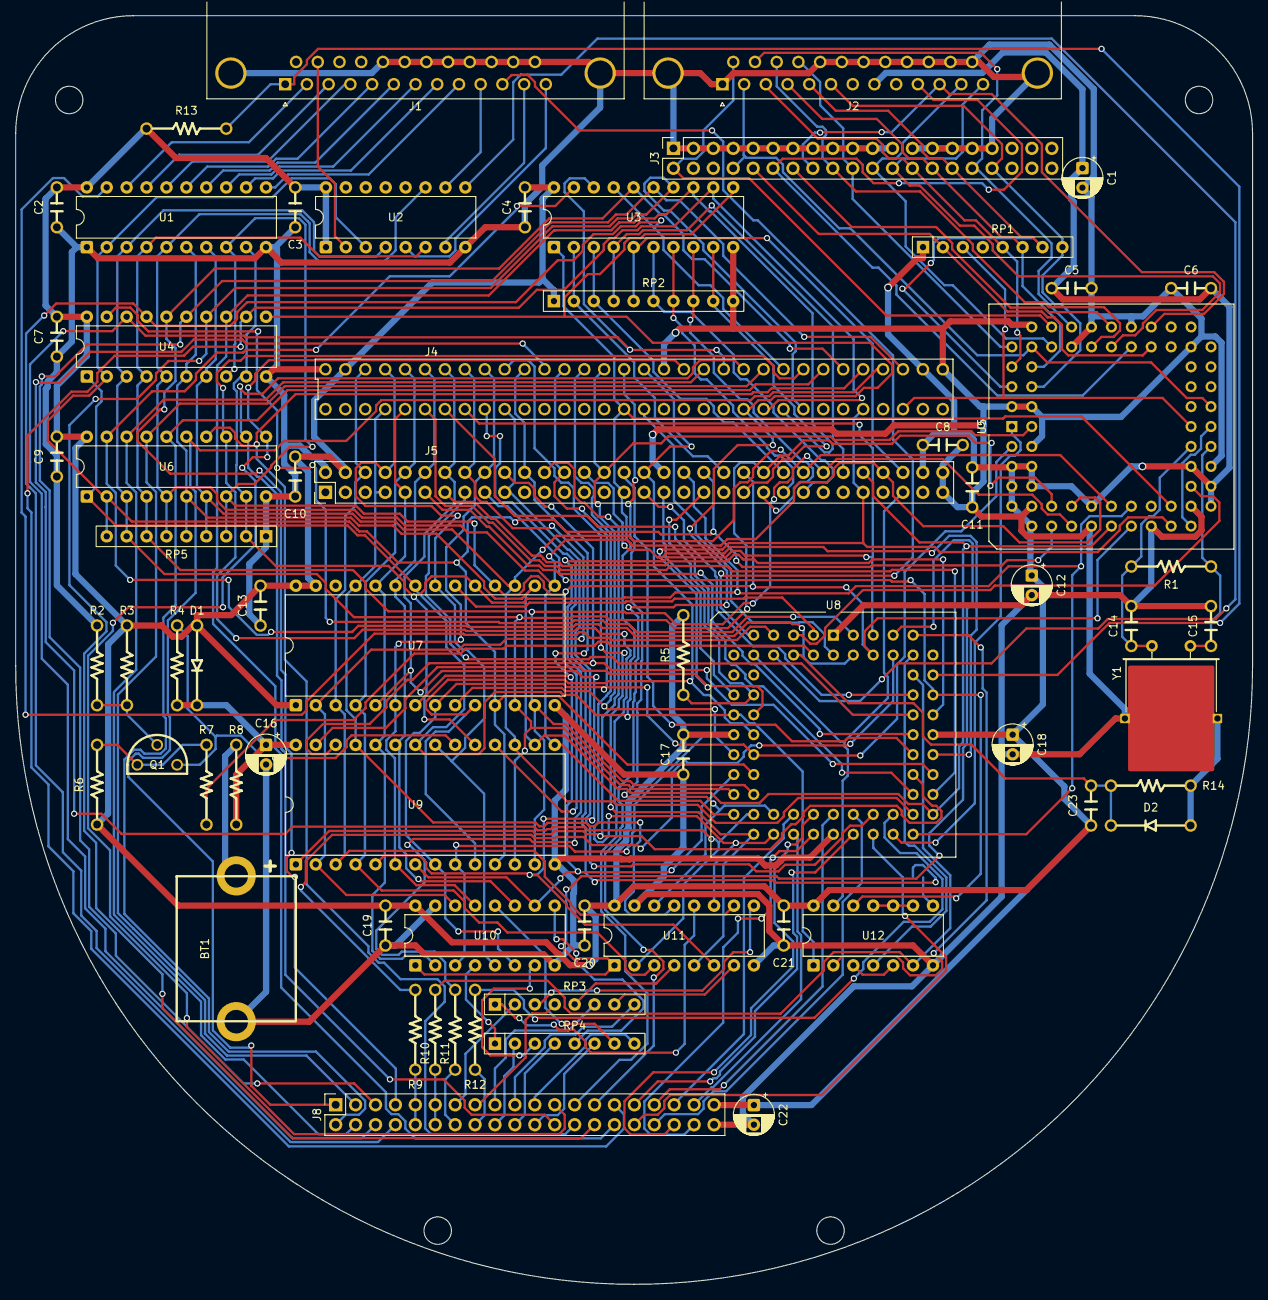
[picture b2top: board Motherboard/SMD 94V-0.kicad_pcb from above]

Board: 2 copper layers, 157.8 x 161.8 mm, 66 parts (1 on the bottom side), 155 nets.
